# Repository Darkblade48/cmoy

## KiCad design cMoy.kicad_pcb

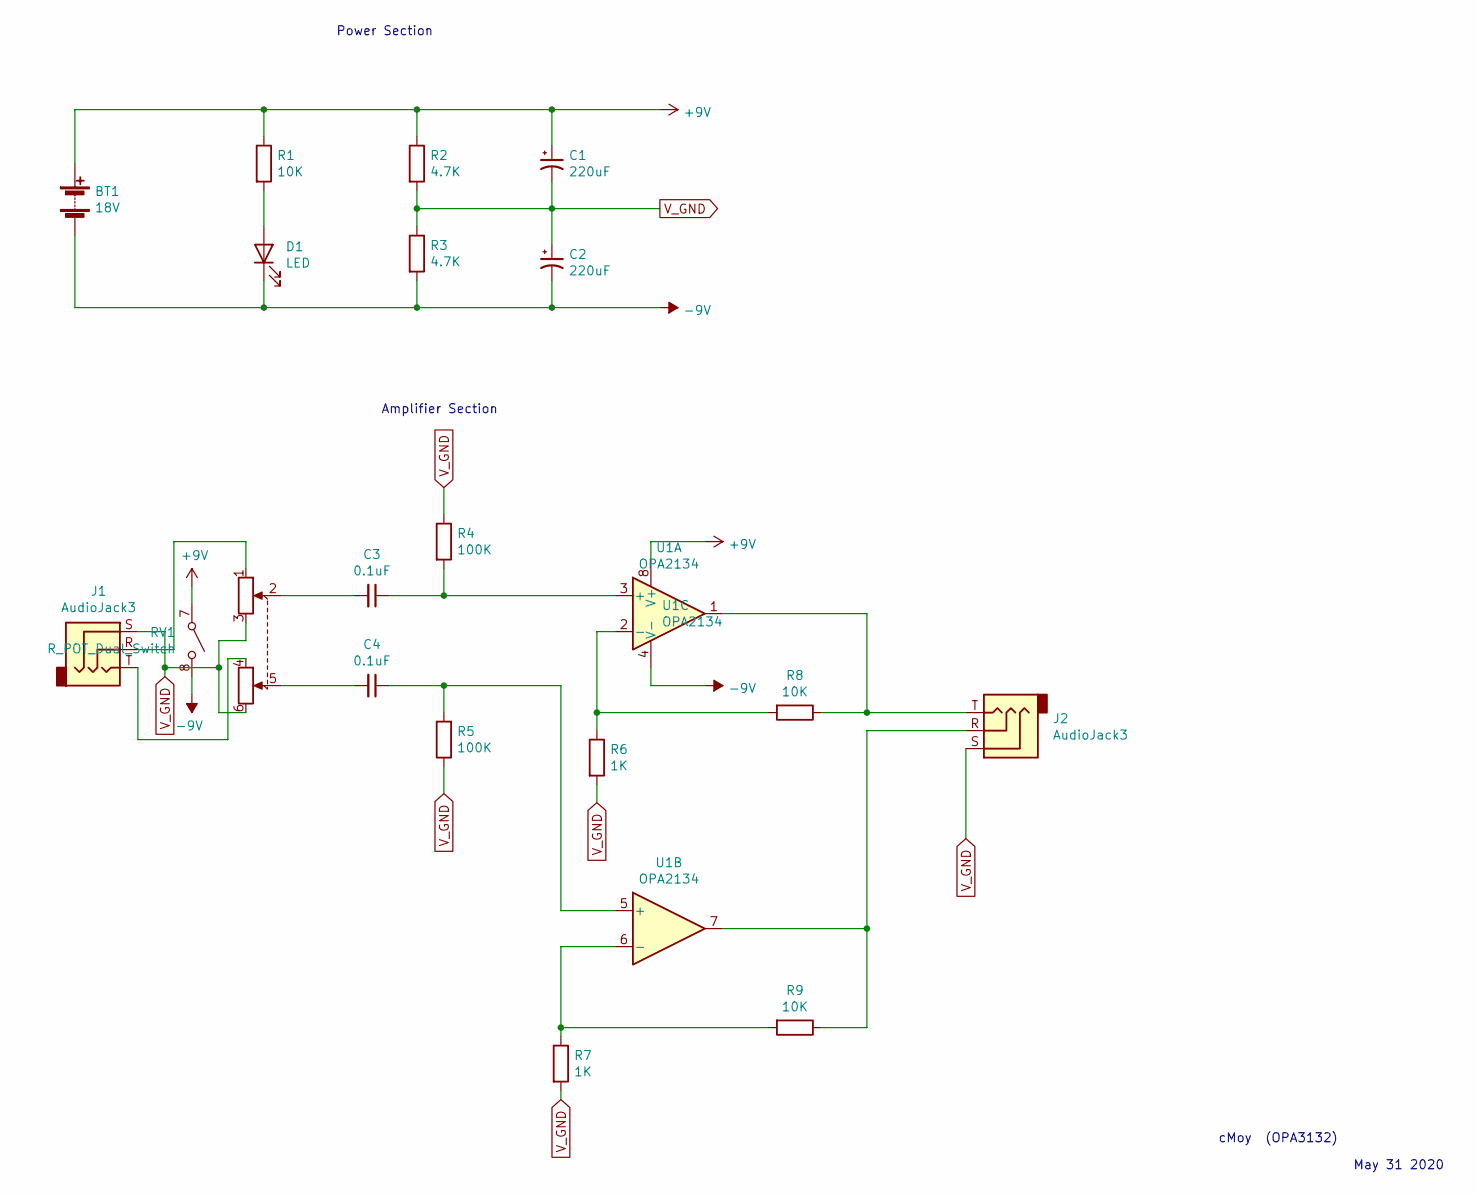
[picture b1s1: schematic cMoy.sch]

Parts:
BT1: 18V; SolderWire-0.15sqmm_1x02_P4mm_D0.5mm_OD1.5mm
C1, C2: 220uF; CP_Radial_D10.0mm_P5.00mm
C3, C4: 0.1uF; C_Rect_L13.0mm_W4.0mm_P10.00mm_FKS3_FKP3_MKS4
D1: LED; LED_D3.0mm
J1, J2: AudioJack3; Jack_3.5mm_Ledino_KB3SPRS_Horizontal
R1, R8, R9: 10K; R_Axial_DIN0207_L6.3mm_D2.5mm_P5.08mm_Vertical
R2, R3: 4.7K; R_Axial_DIN0207_L6.3mm_D2.5mm_P5.08mm_Vertical
R4, R5: 100K; R_Axial_DIN0207_L6.3mm_D2.5mm_P5.08mm_Vertical
R6, R7: 1K; R_Axial_DIN0207_L6.3mm_D2.5mm_P5.08mm_Vertical
RV1: R_POT_Dual_Switch; RK0971221Z05
U1: OPA2134; DIP-8_W7.62mm_Socket_LongPads

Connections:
+9V: BT1.1 (+), C1.1, R1.1, R2.1, RV1.7 (A), U1.8 (V+)
-9V: BT1.2 (-), C2.2, D1.1 (K), R3.2, RV1.8 (B), U1.4 (V-)
unnamed: C3.1, R4.2, U1.3 (+)
unnamed: C3.2, RV1.2
unnamed: C4.1, R5.2, U1.5 (+)
unnamed: C4.2, RV1.5
unnamed: D1.2 (A), R1.2
unnamed: J1.R, RV1.1
unnamed: J1.T, RV1.4
unnamed: J2.R, R9.1, U1.7
unnamed: J2.T, R8.1, U1.1
unnamed: R6.1, R8.2, U1.2 (-)
unnamed: R7.1, R9.2, U1.6 (-)
V_GND: C1.2, C2.1, J1.S, J2.S, R2.2, R3.1, R4.1, R5.1, R6.2, R7.2, RV1.3, RV1.6

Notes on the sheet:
Power Section
cMoy (OPA3132)
May 31 2020
Amplifier Section

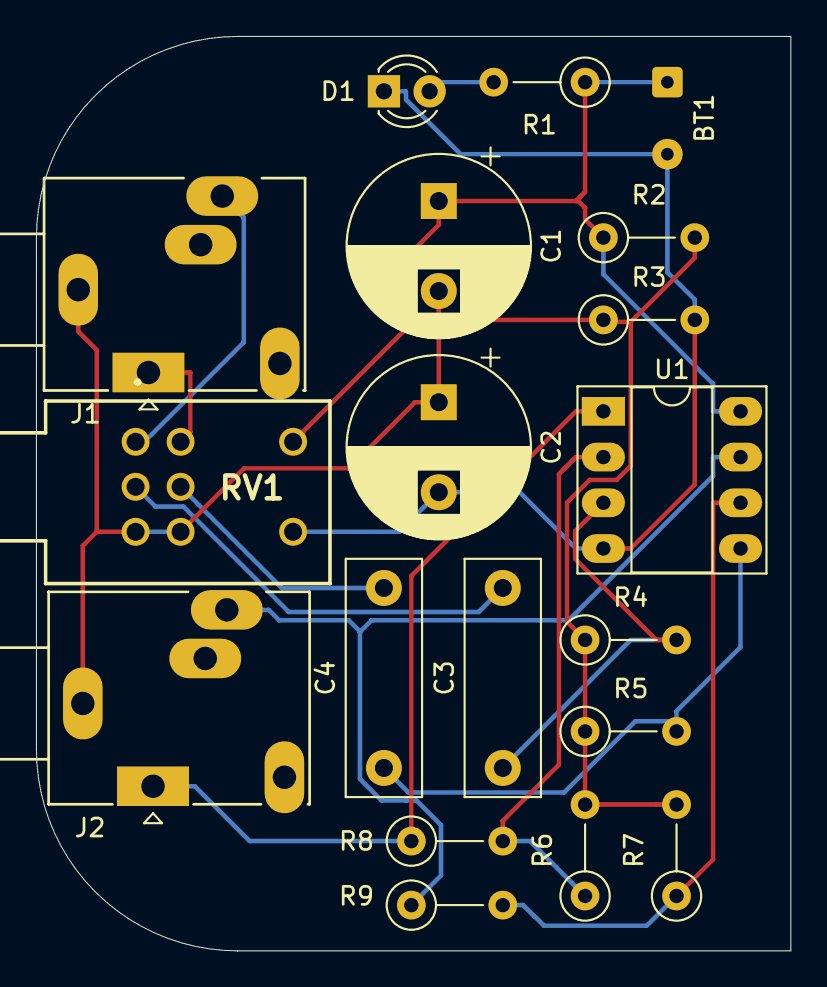
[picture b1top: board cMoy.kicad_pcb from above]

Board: 2 copper layers, 41.9 x 50.8 mm, 19 parts (0 on the bottom side), 14 nets.

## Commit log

2020-06-13 Add files via upload
    Updated June 12 2020
